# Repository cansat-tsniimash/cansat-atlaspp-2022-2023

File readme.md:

Репозитий команды АТЛАС++ на 2022-2023 года

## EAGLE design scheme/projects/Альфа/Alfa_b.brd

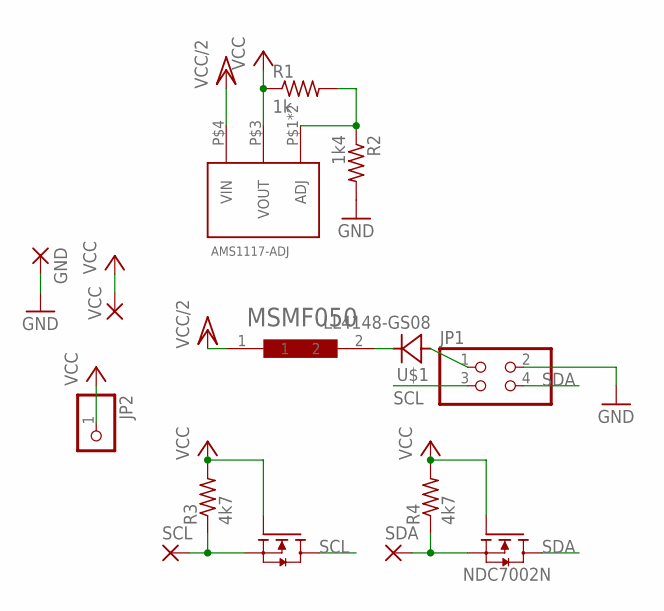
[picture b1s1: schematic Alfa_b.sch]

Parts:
AMS1117-ADJ: AMS1117; SOT223
GND: SMD2; SMD1,27-2,54
JP1: PINHD-2X2; 2X02
JP2: PINHD-1X1; 1X01
MSMF050: MF-MSMF050
NDC7002N: NDC7002N; SOT-23-6
R1: 1k; R0603
R2: 1k4; R0603
R3, R4: 4k7; R0603
SCL: SMD2; SMD1,27-2,54
SDA: SMD2; SMD1,27-2,54
U$1: LL4148-GS08; SOD-80
VCC: SMD2; SMD1,27-2,54

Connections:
GND: GND.1, JP1.2, R2.2
unnamed: MSMF050.2, U$1.2 (C)
unnamed: JP1.1, U$1.1 (A)
unnamed: AMS1117-ADJ.P$1 (ADJ), AMS1117-ADJ.P$2 (ADJ), R1.2, R2.1
unnamed: NDC7002N.5 (S1), R3.1, SCL.1
unnamed: NDC7002N.2 (S2), R4.1, SDA.1
SCL: JP1.3, NDC7002N.6 (D1)
SDA: JP1.4, NDC7002N.4 (D2)
VCC: AMS1117-ADJ.P$3 (VOUT), JP2.1, NDC7002N.1 (G1), NDC7002N.3 (G2), R1.1, R3.2, R4.2, VCC.1
VCC/2: AMS1117-ADJ.P$4 (VIN), MSMF050.1

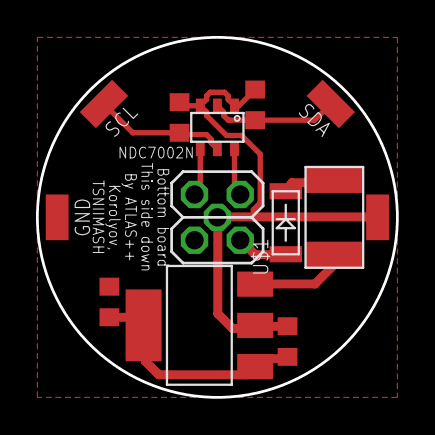
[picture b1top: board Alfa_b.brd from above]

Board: 2 copper layers, 20.0 x 20.0 mm, 14 parts (1 on the bottom side), 10 nets.

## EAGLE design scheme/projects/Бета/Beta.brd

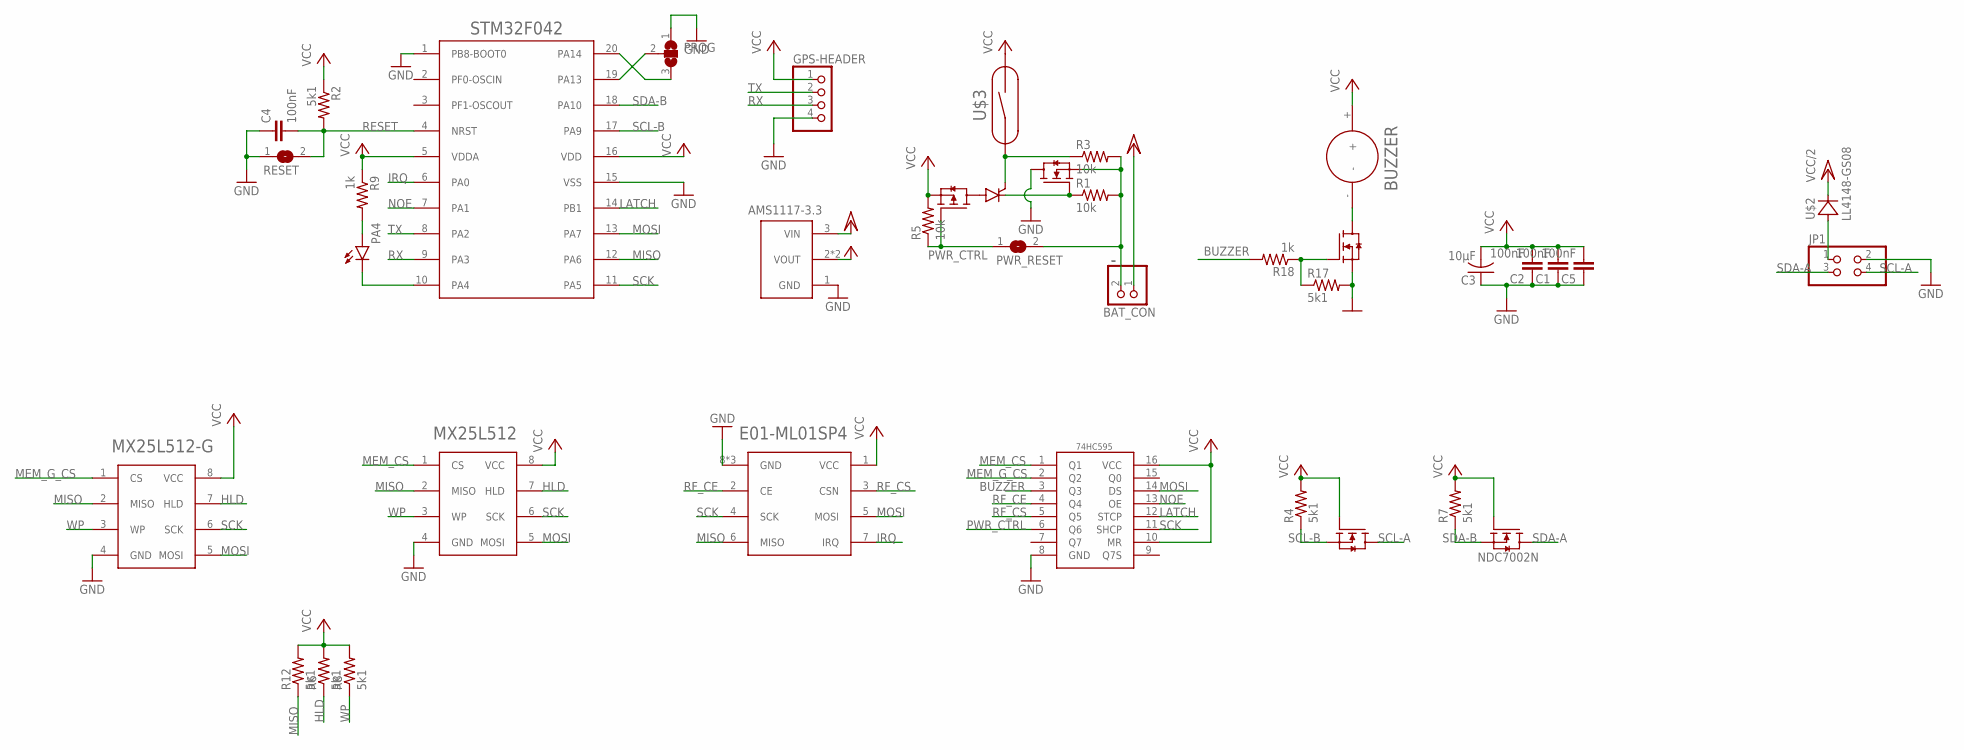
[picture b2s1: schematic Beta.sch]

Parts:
74HC595: 74HC595SOIC16; SOIC16
AMS1117-3.3: AMS1117; SOT223
AO3407: AO3407A; SOT23-3
BAT_CON: PINHD-1X2; 1X02
BUZ: SI2302CDS; SOT23-3
BUZZER: BUZZER-5V; BUZZER
C1, C2, C4, C5: 100nF; C0603
C3: 10µF; C1206
E01-ML01SP4: E01-ML01SP4
GPS-HEADER: PINHD-1X4; 1X04
JP1: PINHD-2X2; 2X02
MX25L512, MX25L512-G: MX25L25645; SOP8
NDC7002N: NDC7002N; SOT-23-6
P0102BL: P0102BL; SOT23-3
PA4: LEDCHIPLED_0603; CHIPLED_0603
PROG: SJ2W; SJ_2
PWR_RESET: SJ
R1, R3, R5: 10k; R0603
R2, R4, R6, R7, R8, R12, R17: 5k1; R0603
R9, R18: 1k; R0603
RESET: SJ
SI2302: SI2302CDS; SOT23-3
STM32F042: STM32F042F6P6; TSSOP-20
U$2: LL4148-GS08; SOD-80
U$3: МКА-07101

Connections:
BUZZER: 74HC595.3 (Q3), R18.2
GND: 74HC595.8 (GND), AMS1117-3.3.1 (GND), BUZ.2 (S), C1.1, C2.1, C3.1, C4.1, C5.1, E01-ML01SP4.8 (GND), E01-ML01SP4.9 (GND), E01-ML01SP4.10 (GND), GPS-HEADER.4, JP1.2, MX25L512.4 (GND), MX25L512-G.4 (GND), PROG.1, R17.2, RESET.1, SI2302.3 (D), STM32F042.1 (PB8-BOOT0), STM32F042.15 (VSS)
GND1: PA4.C, STM32F042.10 (PA4)
HLD: MX25L512.7 (HLD), MX25L512-G.7 (HLD), R6.1
IRQ: E01-ML01SP4.7 (IRQ), STM32F042.6 (PA0)
LATCH: 74HC595.12 (STCP), STM32F042.14 (PB1)
MEM_CS: 74HC595.1 (Q1), MX25L512.1 (CS)
MEM_G_CS: 74HC595.2 (Q2), MX25L512-G.1 (CS)
MISO: E01-ML01SP4.6 (MISO), MX25L512.2 (MISO), MX25L512-G.2 (MISO), R12.1, STM32F042.12 (PA6)
MOSI: 74HC595.14 (DS), E01-ML01SP4.5 (MOSI), MX25L512.5 (MOSI), MX25L512-G.5 (MOSI), STM32F042.13 (PA7)
unnamed: BUZ.3 (D), BUZZER.-
unnamed: PROG.2, STM32F042.19 (PA13)
unnamed: PROG.3, STM32F042.20 (PA14)
unnamed: P0102BL.1 (C), R1.1, SI2302.1 (G)
unnamed: PA4.A, R9.2
unnamed: P0102BL.2 (G), R3.1, U$3.1
unnamed: AO3407.3 (D), P0102BL.3 (A)
unnamed: BAT_CON.2, PWR_RESET.2, R1.2, R3.2, SI2302.2 (S)
unnamed: BUZ.1 (G), R17.1, R18.1
unnamed: JP1.1, U$2.1 (A)
NOE: 74HC595.13 (OE), STM32F042.7 (PA1)
PWR_CTRL: 74HC595.6 (Q6), AO3407.1 (G), PWR_RESET.1, R5.1
RESET: C4.2, R2.2, RESET.2, STM32F042.4 (NRST)
RF_CE: 74HC595.4 (Q4), E01-ML01SP4.2 (CE)
RF_CS: 74HC595.5 (Q5), E01-ML01SP4.3 (CSN)
RX: GPS-HEADER.3, STM32F042.9 (PA3)
SCK: 74HC595.11 (SHCP), E01-ML01SP4.4 (SCK), MX25L512.6 (SCK), MX25L512-G.6 (SCK), STM32F042.11 (PA5)
SCL-A: JP1.4, NDC7002N.6 (D1)
SCL-B: NDC7002N.5 (S1), R4.1, STM32F042.17 (PA9)
SDA-A: JP1.3, NDC7002N.4 (D2)
SDA-B: NDC7002N.2 (S2), R7.1, STM32F042.18 (PA10)
TX: GPS-HEADER.2, STM32F042.8 (PA2)
VCC: 74HC595.10 (MR), 74HC595.16 (VCC), AMS1117-3.3.2 (VOUT), AMS1117-3.3.4 (VOUT), AO3407.2 (S), BUZZER.+, C1.2, C2.2, C3.2, C5.2, E01-ML01SP4.1 (VCC), GPS-HEADER.1, MX25L512.8 (VCC), MX25L512-G.8 (VCC), NDC7002N.1 (G1), NDC7002N.3 (G2), R2.1, R4.2, R5.2, R6.2, R7.2, R8.2, R9.1, R12.2, STM32F042.5 (VDDA), STM32F042.16 (VDD), U$3.2
VCC/2: AMS1117-3.3.3 (VIN), BAT_CON.1, U$2.2 (C)
WP: MX25L512.3 (WP), MX25L512-G.3 (WP), R8.1

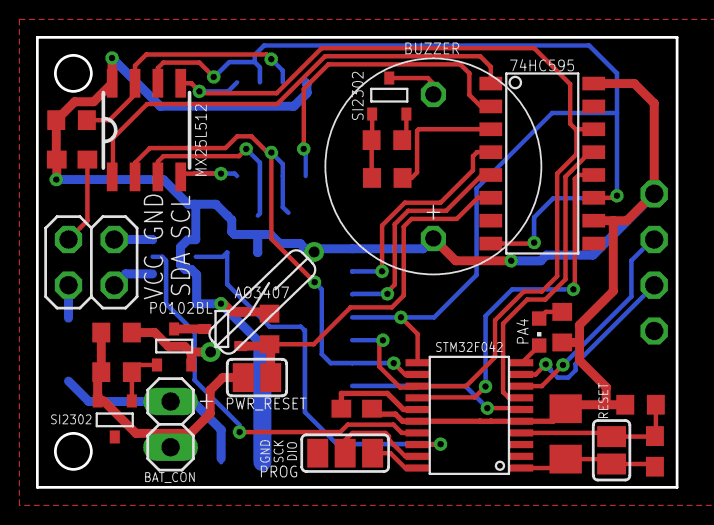
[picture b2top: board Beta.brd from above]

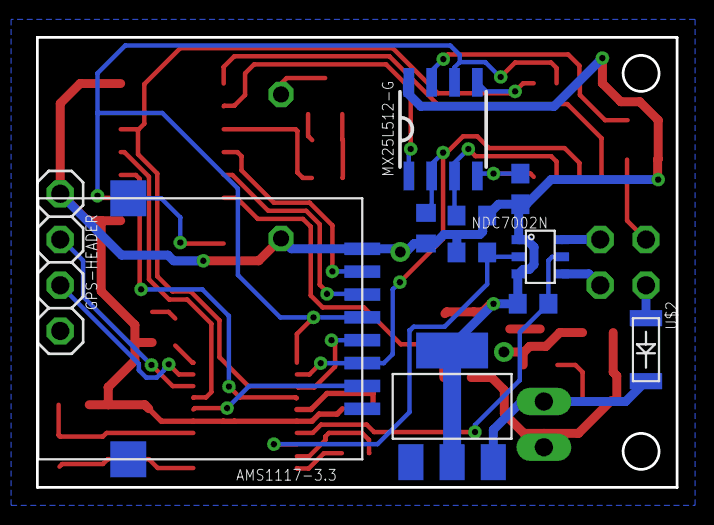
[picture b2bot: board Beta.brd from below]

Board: 2 copper layers, 35.5 x 25.0 mm, 38 parts (11 on the bottom side), 35 nets.

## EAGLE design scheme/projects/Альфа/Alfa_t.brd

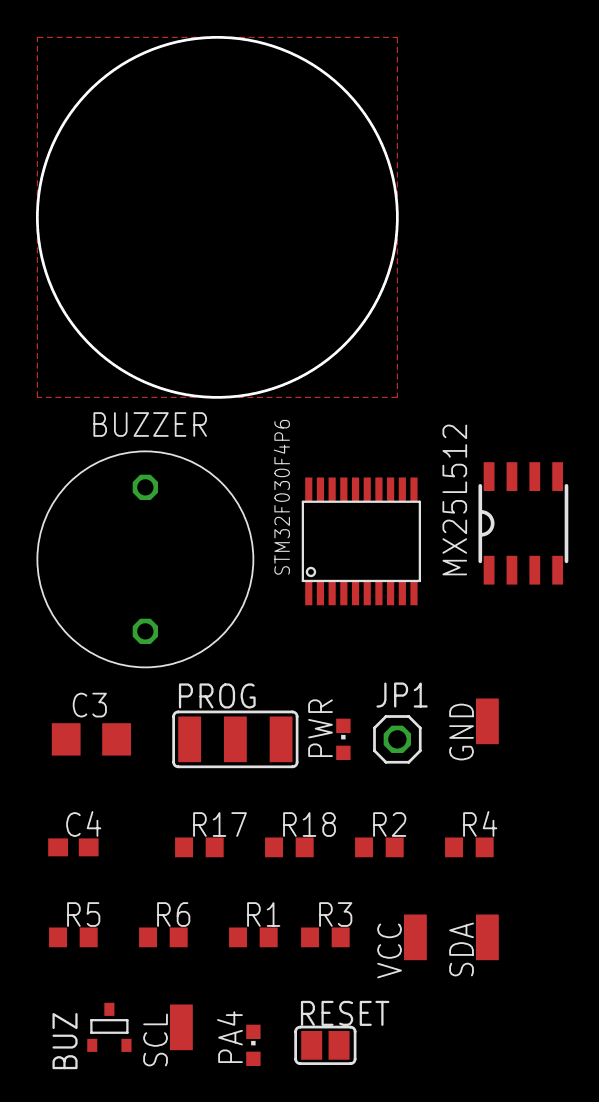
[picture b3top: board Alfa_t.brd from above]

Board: 2 copper layers, 20.0 x 20.0 mm, 23 parts (0 on the bottom side), 21 nets, no tracks yet.

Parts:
BUZ: SI2302CDS; SOT23-3
BUZZER: BUZZER-5V; BUZZER
C3: 10µF; C1206
C4: 100nF; C0603
GND: SMD1,27-2,54
JP1: 1X01
MX25L512: MX25L25645; SOP8
PA4: CHIPLED_0603
PROG: SJ_2W
PWR: CHIPLED_0603
R1, R3, R18: 1k; R0603
R2, R4, R5, R6, R17: 5k1; R0603
RESET: SJ
SCL: SMD1,27-2,54
SDA: SMD1,27-2,54
STM32F030F4P6: STM32F030F4P6; TSSOP-20
VCC: SMD1,27-2,54

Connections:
BUZZER: R18.2, STM32F030F4P6.9
CS: MX25L512.1, STM32F030F4P6.14
GND: BUZ.2, C3.1, C4.1, GND.1, MX25L512.4, PROG.3, PWR.C, R17.2, RESET.1, STM32F030F4P6.1, STM32F030F4P6.15
MISO: MX25L512.2, STM32F030F4P6.12
MOSI: R4.2, STM32F030F4P6.13
unnamed: BUZ.3, BUZZER.-
unnamed: PROG.2, STM32F030F4P6.20
unnamed: PROG.1, STM32F030F4P6.19
unnamed: PWR.A, R3.2
unnamed: PA4.A, R1.2
unnamed: PA4.C, STM32F030F4P6.10
unnamed: JP1.1, STM32F030F4P6.8
unnamed: MX25L512.3, R5.1
unnamed: BUZ.1, R17.1, R18.1
unnamed: MX25L512.5, R4.1
unnamed: MX25L512.7, R6.1
RESET: C4.2, R2.2, RESET.2, STM32F030F4P6.4
SCK: MX25L512.6, STM32F030F4P6.11
SCL: SCL.1, STM32F030F4P6.17
SDA: SDA.1, STM32F030F4P6.18
VCC: BUZZER.+, C3.2, MX25L512.8, R1.1, R2.1, R3.1, R5.2, R6.2, STM32F030F4P6.5, STM32F030F4P6.16, VCC.1

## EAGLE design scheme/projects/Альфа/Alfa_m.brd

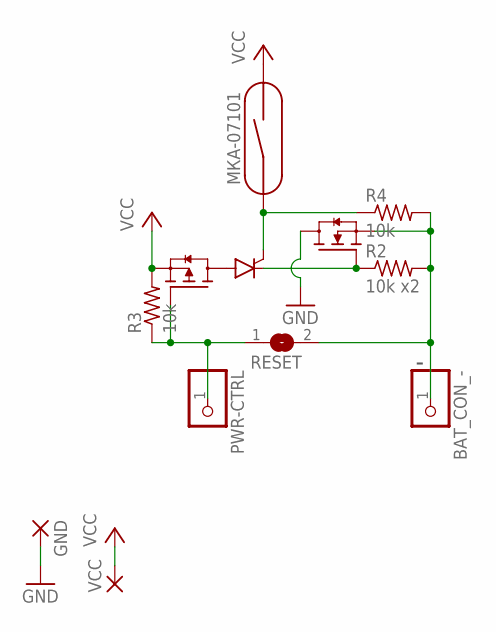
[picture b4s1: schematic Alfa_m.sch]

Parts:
AO3407: AO3407A; SOT23-3
BAT_CON_-: PINHD-1X1; 1X01
GND: SMD2; SMD1,27-2,54
P0102BL: P0102BL; SOT23-3
PWR-CTRL: PINHD-1X1; 1X01
R2: 10k x2; R0603
R3, R4: 10k; R0603
RESET: SJ
SI2302: SI2302CDS; SOT23-3
VCC: SMD2; SMD1,27-2,54
МКА-07101: МКА-07101

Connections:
GND: GND.1, SI2302.3 (D)
unnamed: P0102BL.1 (C), R2.1, SI2302.1 (G)
unnamed: P0102BL.2 (G), R4.1, МКА-07101.1
unnamed: AO3407.3 (D), P0102BL.3 (A)
unnamed: BAT_CON_-.1, R2.2, R4.2, RESET.2, SI2302.2 (S)
unnamed: AO3407.1 (G), PWR-CTRL.1, R3.1, RESET.1
VCC: AO3407.2 (S), R3.2, VCC.1, МКА-07101.2

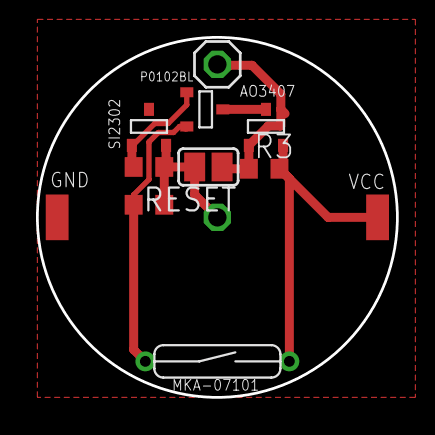
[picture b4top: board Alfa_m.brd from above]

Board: 2 copper layers, 20.0 x 20.0 mm, 12 parts (1 on the bottom side), 7 nets.

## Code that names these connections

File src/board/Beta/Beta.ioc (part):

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Mcu.Name=STM32F042F6Px
Mcu.Package=TSSOP20
Mcu.UserName=STM32F042F6Px
PA0.Signal=GPIO_Input
PA1.GPIOParameters=GPIO_Speed,PinState,GPIO_PuPd,GPIO_Label,GPIO_ModeDefaultOutputPP
PA1.GPIO_Label=oe
PA1.GPIO_ModeDefaultOutputPP=GPIO_MODE_OUTPUT_OD
PA1.GPIO_PuPd=GPIO_PULLUP
PA1.GPIO_Speed=GPIO_SPEED_FREQ_HIGH
PA1.PinState=GPIO_PIN_SET
PA1.Signal=GPIO_Output
PA10.GPIOParameters=GPIO_Pu
PA10.GPIO_Pu=GPIO_PULLUP
PA10.Mode=I2C
PA10.Signal=I2C1_SDA
PA13.Mode=Serial_Wire
PA13.Signal=SYS_SWDIO
PA14.Mode=Serial_Wire
PA14.Signal=SYS_SWCLK
PA2.Mode=Asynchronous
PA2.Signal=USART2_TX
PA3.Mode=Asynchronous
PA3.Signal=USART2_RX
PA4.GPIOParameters=GPIO_PuPd,GPIO_Label,GPIO_ModeDefaultOutputPP
PA4.GPIO_Label=LED
PA4.GPIO_ModeDefaultOutputPP=GPIO_MODE_OUTPUT_PP
PA4.GPIO_PuPd=GPIO_NOPULL
PA4.Signal=GPIO_Output
PA5.Mode=Full_Duplex_Master
PA5.Signal=SPI1_SCK
PA6.Mode=Full_Duplex_Master
PA6.Signal=SPI1_MISO
PA7.Mode=Full_Duplex_Master
PA7.Signal=SPI1_MOSI
PA9.GPIOParameters=GPIO_Pu
PA9.GPIO_Pu=GPIO_PULLUP
PA9.Mode=I2C
PA9.Signal=I2C1_SCL
PB1.GPIOParameters=GPIO_Label
PB1.GPIO_Label=latch
PB1.Signal=GPIO_Output
RCC.SYSCLKFreq_VALUE=48000000
RCC.SYSCLKSource=RCC_SYSCLKSOURCE_HSI48
board=custom

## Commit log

2022-11-05 Добавил задержку в 100мс/ /Added delay 100ms
2022-11-12 Начинаем
2022-11-12 Добавил метаданные в гитигнор
2022-11-12 Create empty project, add to ignore: .settings and Debug/ /Создал пустой проэкт, добавил в игнор: .settings and Debug
2022-11-12 Создал пустой проекта для теста I2C Slave
2022-11-12 Костыли для i2c. Будем тестить
2022-11-12 Прописали в костыль конкретные пины/ /Wrote specific pins to crutch
2022-11-12 Прописал конкретные пины
2022-11-12 Написал приём байта по I2C
2022-11-12 Написал отправку байта по I2C/ /Wrote byte sending using I2C
2022-11-12 создал проэкт, добавил измерения давления тмпературы влажности и высоты
2022-11-12 Добавил гироскоп и акселерометр
2022-11-16 Добавил магнитометр по LIS
2022-11-19 Добавил структуру, поменял отправляемое значение, наладил отправку/ /Added struct, change the sent value, adjusted sending
2022-11-19 Дописал приём
2022-11-19 Заменил массив на структуру
2022-11-19 Добавила сабмодуль с библиотекой
2022-11-26 Добавлены фоторезистор и DS18, DS18 не работает
2022-12-10 Написал код для получения чего-то по радио
2022-12-10 Написал код для отправки чего-то по радио
2022-12-14 Написал код на ATGM336H/Wrote code on ATGM336H
2023-02-11 Beta
2023-02-11 Последние изменения GPSски Артем работай
2023-02-11 платы
2023-02-11 Приемка-наземка на петухоне
2023-02-18 Код для радио
2023-02-18 Добавил отправку на sd
2023-02-22 Дописал Test_I2C, вроде норм
2023-03-03 Написал в цикле проверку на ошибки I2C.
2023-03-04 Начал переписывать флаги в its-i2c-link
2023-03-10 Задебажил ашипки(остались только флаги!)
2023-03-10 Хэдэры которые проспали
2023-03-11 Код для теста i2c на аппарат
2023-03-11 ничего не сделал
2023-03-11 Теперь это вроде собирается
2023-03-11 чета вроде сделал
2023-03-11 еще чета
2023-03-17 Запущен i2c-link (на новой cube-ide, поэтому требует правок)
2023-03-17 статус заполнил и чета с сд сделал но оно не работает
2023-03-18 Написал подчинённую часть I2C | БЕТА
2023-03-22 Приготовились к тестам
2023-03-24 Полный проект под новый cubemx
2023-03-25 Настройка СД
2023-03-25 я жеска сделал сд оно работает
2023-03-25 я супер мега жеска сделал сд и оно супер мега круто работает дайте денег
2023-03-25 Супер ультра мега гелекси жеска сделал так чтоб дс до десятых было
2023-03-27 Заигнорил лишнее
2023-03-27 Сихнронизация сабмодуля
2023-03-27 Сборка новой cubeide (+ добавление забытых генерированных файлов)
2023-03-27 Все работает
2023-03-29 Передача работает, идём проверять дальше(типо уверенно, спасити(()
2023-03-29 самая жеская отправка по ай ту си 1 2 пол третьей и четвертая комманды сделаны
2023-03-29 Перенесли While, продолжаем тестить
2023-03-31 сделал самые жеские в мире состояния и там лампочки мигают по кайфу а еще сд в хард фолт не гг
2023-04-01 Написали функцию рид
2023-04-01 ПРОШЛЫЙ КОММИТ НЕ МОЙ Я ДЕЛАЮ ТОЛЬКО НОРМАЛЬНЫЕ КОММИТЫ ЭТО ПЕРВО АПРЕЛЬСКАЯ ШУТКА Сделал самую жескю функцию рид но там чета не работает дальше лень
2023-04-05 жеска добавили ожидание
2023-04-05 Забыл заполнить csv_file.h, но не забыл перенести структуры в отдельный хэдр + добавил запись в csv файлы
2023-04-07 я самый жеский и сделал проверку жускую там все пишет вообще класс(прошлый коммит не мой)
2023-04-07 Перегенерировал код
2023-04-08 Подправил запись цсв
2023-04-14 Наладили работу в режиме слейва на I2C:
    1. Выключили SlaveByteControl;
    2. Обработку ADDR флагов перенесли после стопов, так как они влетают
    похоже одновременно;
    3. Добавили чистку TX регистра после внезапных остановок DMA
2023-04-22 Начали тестить, СР работает, но время на костылях. Радио потестить не удалось, возможен конфликт с СР
2023-04-28 Дописали и потестили радио на ЧЯ
2023-04-28 Начали переписывать команды i2c на ОА
2023-04-28 покайфу написал ай ту си супер мега жеска
2023-04-29 Начал переписывать протокол I2C
2023-04-29 Предпринята попытка завести память
2023-04-29 Радио работает
2023-05-03 Недостающие файлы
2023-05-03 Починила проект
2023-05-12 САМАЯ ЖЕСКАЯ ДЖИПИЭСКА ПАЧАЛА ПРИНИМАТЬ НОРМАЛЬНО КАЙФ ЭЩКЕРЕЕЕЕЕЕ
2023-05-12 Недостающие файлы библиотек
2023-05-17 чутка дописал I2C погода сегодня хорошая, только ветерок ай-ай
2023-05-17 Парсер для Беты ветерок ай-ай
2023-05-17 проверка путей(
2023-05-19 навсякий перед пуллом
2023-05-20 Самая жеская гамма в мире эщкере
2023-05-20 Правки гаммы для сборки + библиотека
2023-05-24 изменили настройки радио и расскомитил что закомитили
2023-05-24 Сделал структуру для настроек передаваемых с ОА (у меня сегодня шторы)
2023-05-27 Жеска засолил гамму
2023-05-27 Самая жеская связь по i2c с ЧОРНИМИ ящиками
2023-05-31 Тестим i2c
2023-05-31 Проверили протокол общения ЧЯ по i2c
2023-05-31 Альфа
2023-06-02 Сделал самую жескую чета там с циклограммой все отправляется с оа на чя ЭЩКЕРЕЕЕЕ
2023-06-02 Сделал жескую отправку покета по радио с ЧОРного ящика ЭЩКЕРЕЕЕЕЕ
2023-06-03 Сделал CSV парсер для ОА и Беты + страые правки приемника беты Я КОМИЧУ ЧЕРЕЗ ТЕРМИНАЛ НА ЛИНУКСЕ)
2023-06-03 Жеска подфиксил бету
2023-06-03 Жеска засолил гамму ЭЩКЕРЕЕЕЕ
2023-06-03 ЖЕСКА ЗАСОЛИЛ 3ИЕ УСТРОЙСТВО ЭЩКЕРЕЕЕЕЕЕ(чета не работает)
2023-06-07 ИСправления для СД карты
2023-06-07 Жеска добавил 3 файла для бетты гаммы и обычный хз че это Let's get it
2023-06-09 ЖЕСКА ДОСОЛИЛ 3ИЕ УСТРОЙСТВО ЭЩКЕРЕЕЕЕЕЕЕ = LET'S GET IT
2023-06-10 Альфа пуш мега прощаюсь с виндовс ((
2023-06-10 Флаги короче сделали как Василий сказал
2023-06-12 Изменения в проектах по результатам тестов плат. Код с тестовым циклом
2023-06-13 Очередные тесты плат. все по отдельности работает
2023-06-14 ТЕПЕРЬ 6ТИ СЛОТОВОЕ 3ИЕ УСТРОЙСТВО ИДЕТ СНОСИТЬ ВАМ ТРОН
2023-06-24 Добавлены функции проверки радобоспособности, сигналы светодиодом и пищалкой
2023-06-24 Проверили радио, поменяли длинну времени для всех пакетов
2023-06-24 Поменяли настройки(как в ПЗ), написали красивенькие состояния, поправили все
2023-06-24 Подогнал под новую версию
2023-06-27 Заводим i2c
2023-06-28 Написал состояния Альфы, Беты, Гаммы, MOUNT(SD)
2023-06-28 Жеска напИсали проверку ай2си ЧЯ и адресацию на альфе ЭЩКЕРЕЕЕЕЕЕ fix
2023-06-28 fix alpha beta gamma
2023-06-30 кайф жеский по памяти
2023-06-30 fix чета память кайф
2023-07-01 КАЙA КОНКРЕТНЫЙ ЭЩКЕРЕЕЕЕЕЕЕЕЕЕЕ ЮХУУУУУ fix
2023-07-03 эталонные данные с ОА, с радио закину завтра
2023-11-04 Еще правки
2023-11-04 Какие-то изменения
